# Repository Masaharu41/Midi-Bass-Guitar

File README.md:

This is the Repository for a project to create a bass guitar that features a mechanical interface that is controlled with MIDI.
  Project development was headed by Owen Fujii. The purpose of the project is to improve upon the prior MIDI controlled bass 
  guitar.

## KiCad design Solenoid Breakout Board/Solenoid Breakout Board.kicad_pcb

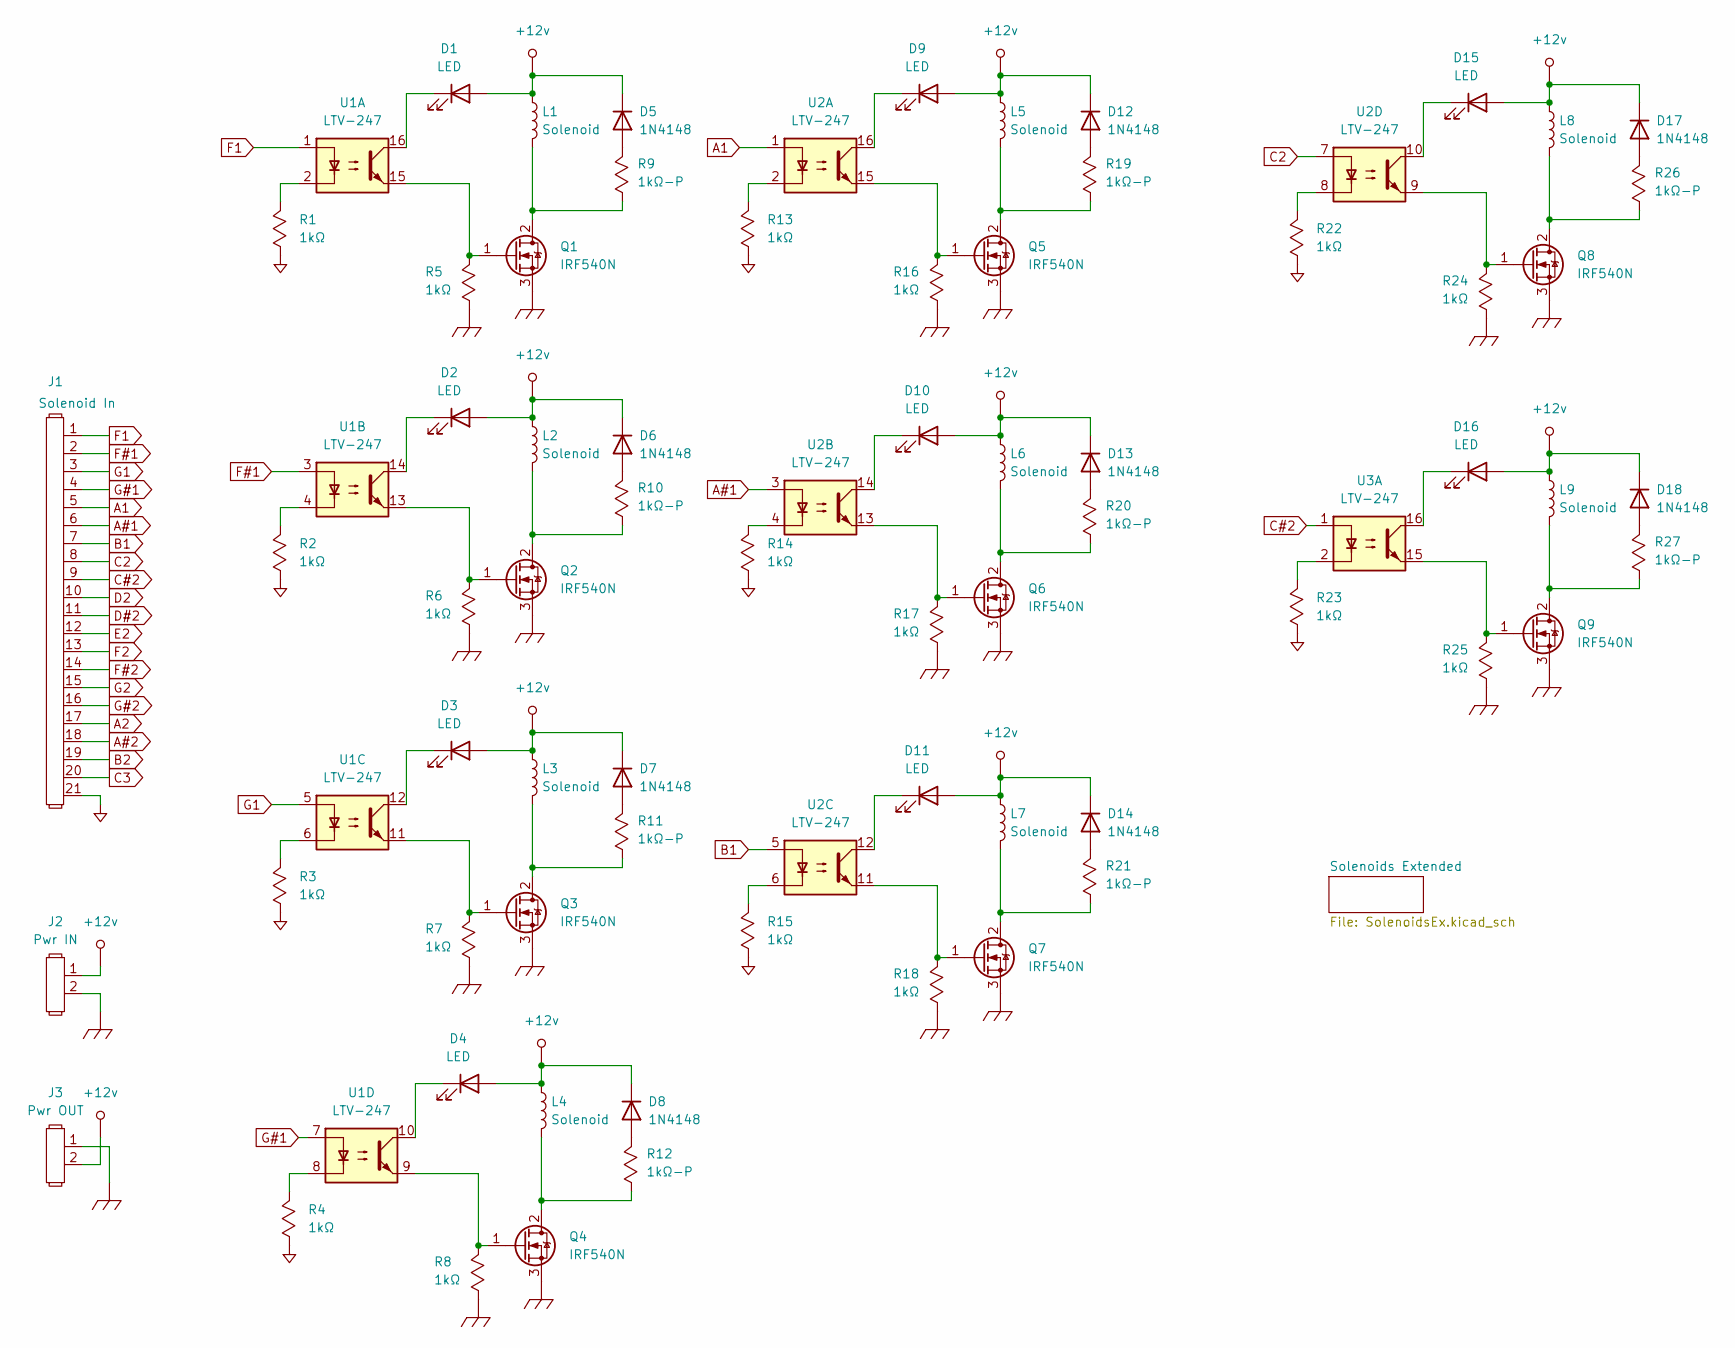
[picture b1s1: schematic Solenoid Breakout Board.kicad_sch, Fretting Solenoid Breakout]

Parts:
D1, D2, D3, D4, D9, D10, D11, D15, D16: LED; LED_0805_2012Metric_Pad1.15x1.40mm_HandSolder
D5, D6, D7, D8, D12, D13, D14, D17, D18: 1N4148; LED_0805_2012Metric_Pad1.15x1.40mm_HandSolder
J1: Solenoid In; PinHeader_1x21_P2.54mm_Vertical
J2: Pwr IN; Two_Pin_Screw_Terminal
J3: Pwr OUT; Two_Pin_Screw_Terminal
L1, L2, L3, L4, L5, L6, L7, L8, L9: Solenoid; Small Expanded TH
Q1, Q2, Q3, Q4, Q5, Q6, Q7, Q8, Q9: IRF540N; TO-220-3_Horizontal_TabUp
R1, R2, R3, R4, R5, R6, R7, R8, R13, R14, R15, R16, R17, R18, R22, R23, R24, R25: 1kΩ; R_0805_2012Metric_Pad1.20x1.40mm_HandSolder
R9, R10, R11, R12, R19, R20, R21, R26, R27: 1kΩ-P; R_1206_3216Metric_Pad1.30x1.75mm_HandSolder
U1, U2, U3: LTV-247; SOP-16_4.4x10.4mm_P1.27mm

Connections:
+12v: D1.2 (A), D2.2 (A), D3.2 (A), D4.2 (A), D5.1 (K), D6.1 (K), D7.1 (K), D8.1 (K), D9.2 (A), D10.2 (A), D11.2 (A), D12.1 (K), D13.1 (K), D14.1 (K), D15.2 (A), D16.2 (A), D17.1 (K), D18.1 (K), J2.1, J3.2, L1.1, L2.1, L3.1, L4.1, L5.1, L6.1, L7.1, L8.1, L9.1; also elsewhere on the board
A1: J1.5, U2.1
A2: J1.17; also elsewhere on the board
A#1: J1.6, U2.3
A#2: J1.18; also elsewhere on the board
B1: J1.7, U2.5
B2: J1.19; also elsewhere on the board
C2: J1.8, U2.7
C3: J1.20; also elsewhere on the board
C#2: J1.9, U3.1
Chassis_GND: J2.2, J3.1, Q1.3 (S), Q2.3 (S), Q3.3 (S), Q4.3 (S), Q5.3 (S), Q6.3 (S), Q7.3 (S), Q8.3 (S), Q9.3 (S), R5.1, R6.1, R7.1, R8.1, R16.1, R17.1, R18.1, R24.1, R25.1; also elsewhere on the board
D2: J1.10; also elsewhere on the board
D#2: J1.11; also elsewhere on the board
E2: J1.12; also elsewhere on the board
F1: J1.1, U1.1
F2: J1.13; also elsewhere on the board
F#1: J1.2, U1.3
F#2: J1.14; also elsewhere on the board
G1: J1.3, U1.5
G2: J1.15; also elsewhere on the board
G#1: J1.4, U1.7
G#2: J1.16; also elsewhere on the board
GND: J1.21, R1.1, R2.1, R3.1, R4.1, R13.1, R14.1, R15.1, R22.1, R23.1; also elsewhere on the board
unnamed: D1.1 (K), U1.16
unnamed: D2.1 (K), U1.14
unnamed: D3.1 (K), U1.12
unnamed: D4.1 (K), U1.10
unnamed: D5.2 (A), R9.2
unnamed: D6.2 (A), R10.2
unnamed: D7.2 (A), R11.2
unnamed: D8.2 (A), R12.2
unnamed: D9.1 (K), U2.16
unnamed: D10.1 (K), U2.14
unnamed: D11.1 (K), U2.12
unnamed: D12.2 (A), R19.2
unnamed: D13.2 (A), R20.2
unnamed: D14.2 (A), R21.2
unnamed: D15.1 (K), U2.10
unnamed: D16.1 (K), U3.16
unnamed: D17.2 (A), R26.2
unnamed: D18.2 (A), R27.2
unnamed: L1.2, Q1.2 (D), R9.1
unnamed: Q1.1 (G), R5.2, U1.15
unnamed: L2.2, Q2.2 (D), R10.1
unnamed: Q2.1 (G), R6.2, U1.13
unnamed: L3.2, Q3.2 (D), R11.1
unnamed: Q3.1 (G), R7.2, U1.11
unnamed: L4.2, Q4.2 (D), R12.1
unnamed: Q4.1 (G), R8.2, U1.9
unnamed: L5.2, Q5.2 (D), R19.1
unnamed: Q5.1 (G), R16.2, U2.15
unnamed: L6.2, Q6.2 (D), R20.1
unnamed: Q6.1 (G), R17.2, U2.13
unnamed: L7.2, Q7.2 (D), R21.1
unnamed: Q7.1 (G), R18.2, U2.11
unnamed: L8.2, Q8.2 (D), R26.1
unnamed: Q8.1 (G), R24.2, U2.9
unnamed: L9.2, Q9.2 (D), R27.1
unnamed: Q9.1 (G), R25.2, U3.15
unnamed: R1.2, U1.2
unnamed: R2.2, U1.4
unnamed: R3.2, U1.6
unnamed: R4.2, U1.8
unnamed: R13.2, U2.2
unnamed: R14.2, U2.4
unnamed: R15.2, U2.6
unnamed: R22.2, U2.8
unnamed: R23.2, U3.2

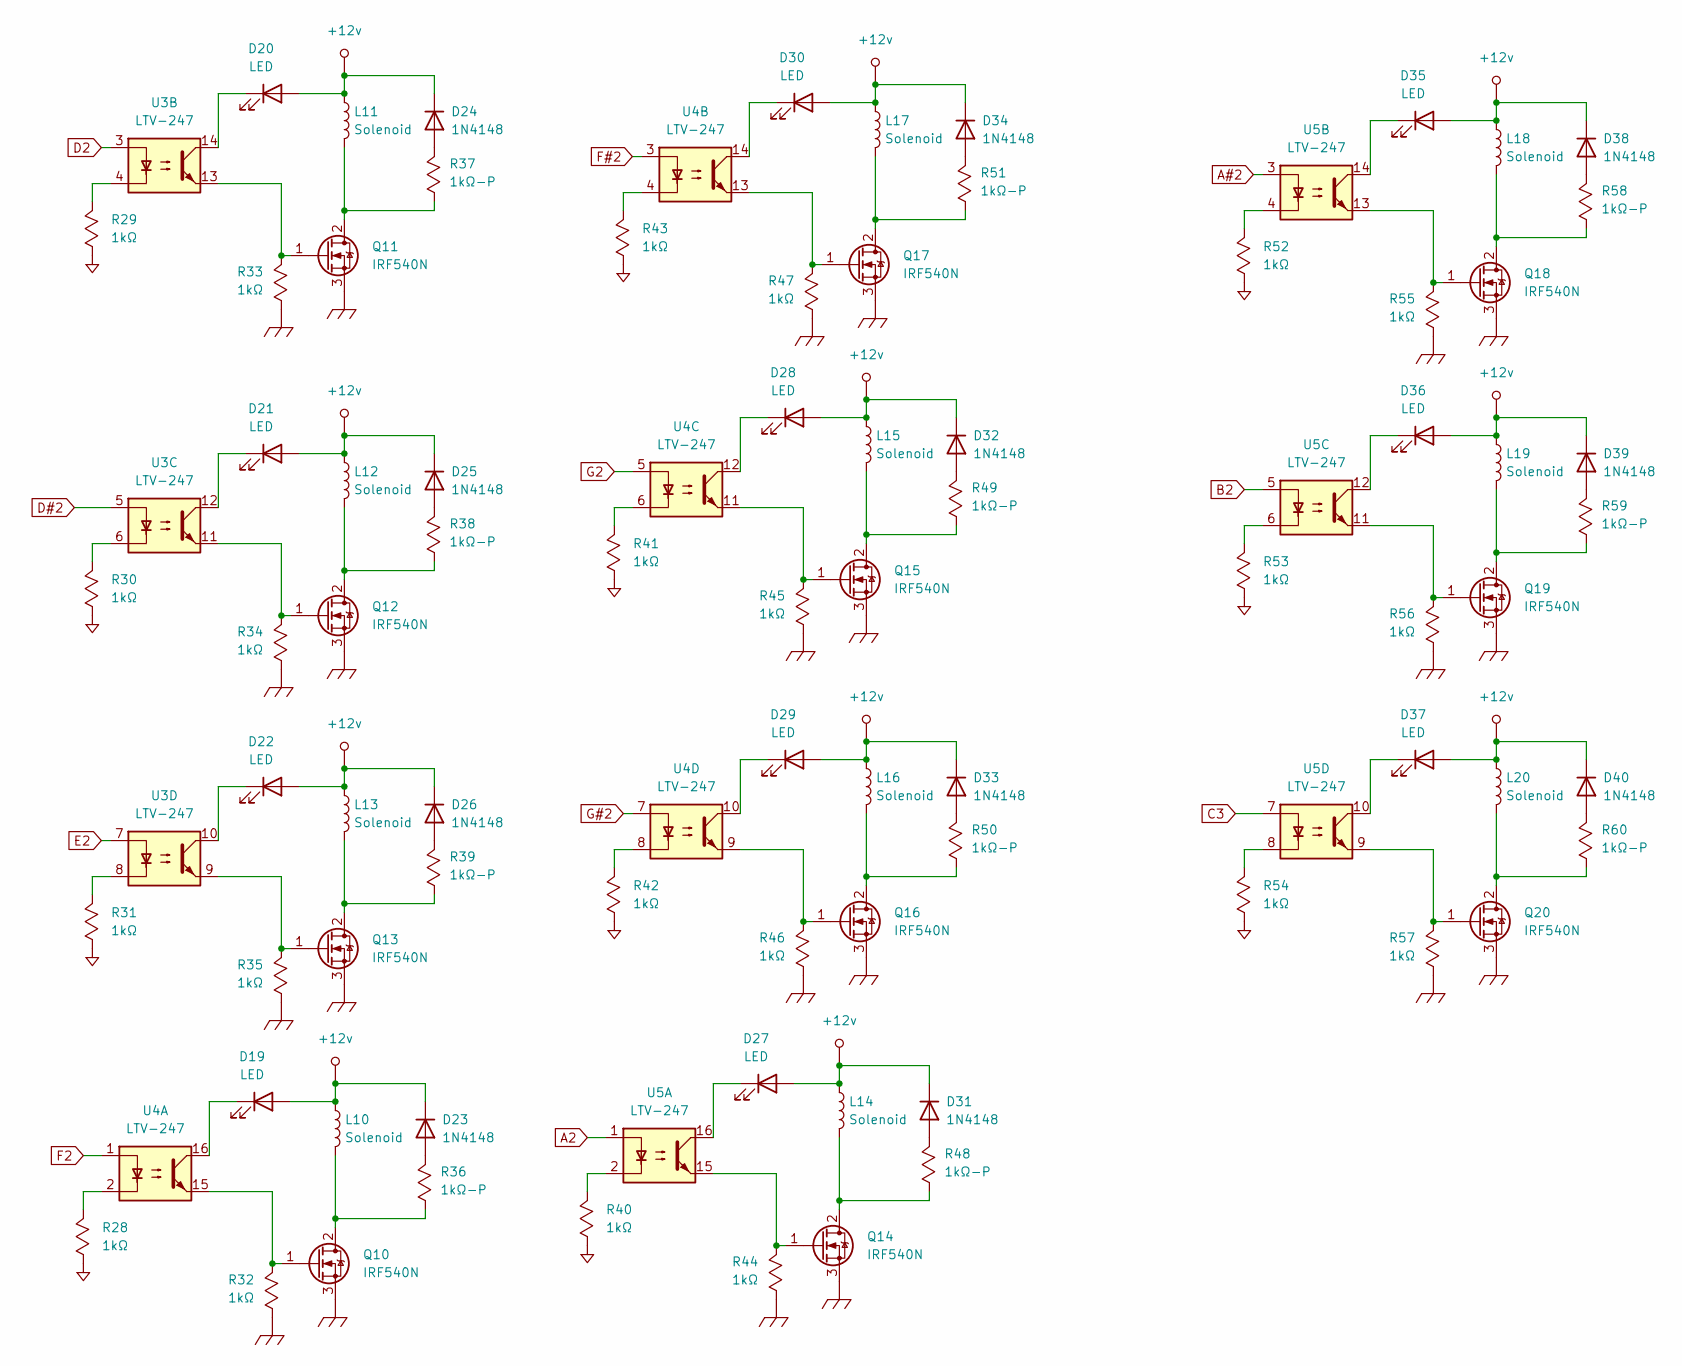
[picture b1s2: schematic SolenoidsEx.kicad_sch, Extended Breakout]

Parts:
D19, D20, D21, D22, D27, D28, D29, D30, D35, D36, D37: LED; LED_0805_2012Metric_Pad1.15x1.40mm_HandSolder
D23, D24, D25, D26, D31, D32, D33, D34, D38, D39, D40: 1N4148; LED_0805_2012Metric_Pad1.15x1.40mm_HandSolder
L10, L11, L12, L13, L14, L15, L16, L17, L18, L19, L20: Solenoid; Small Expanded TH
Q10, Q11, Q12, Q13, Q14, Q15, Q16, Q17, Q18, Q19, Q20: IRF540N; TO-220-3_Horizontal_TabUp
R28, R29, R30, R31, R32, R33, R34, R35, R40, R41, R42, R43, R44, R45, R46, R47, R52, R53, R54, R55, R56, R57: 1kΩ; R_0805_2012Metric_Pad1.20x1.40mm_HandSolder
R36, R37, R38, R39, R48, R49, R50, R51, R58, R59, R60: 1kΩ-P; R_1206_3216Metric_Pad1.30x1.75mm_HandSolder
U3, U4, U5: LTV-247; SOP-16_4.4x10.4mm_P1.27mm

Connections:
+12v: D19.2 (A), D20.2 (A), D21.2 (A), D22.2 (A), D23.1 (K), D24.1 (K), D25.1 (K), D26.1 (K), D27.2 (A), D28.2 (A), D29.2 (A), D30.2 (A), D31.1 (K), D32.1 (K), D33.1 (K), D34.1 (K), D35.2 (A), D36.2 (A), D37.2 (A), D38.1 (K), D39.1 (K), D40.1 (K), L10.1, L11.1, L12.1, L13.1, L14.1, L15.1, L16.1, L17.1, L18.1, L19.1, L20.1; also elsewhere on the board
A2: U5.1; also elsewhere on the board
A#2: U5.3; also elsewhere on the board
B2: U5.5; also elsewhere on the board
C3: U5.7; also elsewhere on the board
Chassis_GND: Q10.3 (S), Q11.3 (S), Q12.3 (S), Q13.3 (S), Q14.3 (S), Q15.3 (S), Q16.3 (S), Q17.3 (S), Q18.3 (S), Q19.3 (S), Q20.3 (S), R32.1, R33.1, R34.1, R35.1, R44.1, R45.1, R46.1, R47.1, R55.1, R56.1, R57.1; also elsewhere on the board
D2: U3.3; also elsewhere on the board
D#2: U3.5; also elsewhere on the board
E2: U3.7; also elsewhere on the board
F2: U4.1; also elsewhere on the board
F#2: U4.3; also elsewhere on the board
G2: U4.5; also elsewhere on the board
G#2: U4.7; also elsewhere on the board
GND: R28.1, R29.1, R30.1, R31.1, R40.1, R41.1, R42.1, R43.1, R52.1, R53.1, R54.1; also elsewhere on the board
unnamed: D19.1 (K), U4.16
unnamed: D20.1 (K), U3.14
unnamed: D21.1 (K), U3.12
unnamed: D22.1 (K), U3.10
unnamed: D23.2 (A), R36.2
unnamed: D24.2 (A), R37.2
unnamed: D25.2 (A), R38.2
unnamed: D26.2 (A), R39.2
unnamed: D27.1 (K), U5.16
unnamed: D28.1 (K), U4.12
unnamed: D29.1 (K), U4.10
unnamed: D30.1 (K), U4.14
unnamed: D31.2 (A), R48.2
unnamed: D32.2 (A), R49.2
unnamed: D33.2 (A), R50.2
unnamed: D34.2 (A), R51.2
unnamed: D35.1 (K), U5.14
unnamed: D36.1 (K), U5.12
unnamed: D37.1 (K), U5.10
unnamed: D38.2 (A), R58.2
unnamed: D39.2 (A), R59.2
unnamed: D40.2 (A), R60.2
unnamed: L10.2, Q10.2 (D), R36.1
unnamed: Q10.1 (G), R32.2, U4.15
unnamed: L11.2, Q11.2 (D), R37.1
unnamed: Q11.1 (G), R33.2, U3.13
unnamed: L12.2, Q12.2 (D), R38.1
unnamed: Q12.1 (G), R34.2, U3.11
unnamed: L13.2, Q13.2 (D), R39.1
unnamed: Q13.1 (G), R35.2, U3.9
unnamed: L14.2, Q14.2 (D), R48.1
unnamed: Q14.1 (G), R44.2, U5.15
unnamed: L15.2, Q15.2 (D), R49.1
unnamed: Q15.1 (G), R45.2, U4.11
unnamed: L16.2, Q16.2 (D), R50.1
unnamed: Q16.1 (G), R46.2, U4.9
unnamed: L17.2, Q17.2 (D), R51.1
unnamed: Q17.1 (G), R47.2, U4.13
unnamed: L18.2, Q18.2 (D), R58.1
unnamed: Q18.1 (G), R55.2, U5.13
unnamed: L19.2, Q19.2 (D), R59.1
unnamed: Q19.1 (G), R56.2, U5.11
unnamed: L20.2, Q20.2 (D), R60.1
unnamed: Q20.1 (G), R57.2, U5.9
unnamed: R28.2, U4.2
unnamed: R29.2, U3.4
unnamed: R30.2, U3.6
unnamed: R31.2, U3.8
unnamed: R40.2, U5.2
unnamed: R41.2, U4.6
unnamed: R42.2, U4.8
unnamed: R43.2, U4.4
unnamed: R52.2, U5.4
unnamed: R53.2, U5.6
unnamed: R54.2, U5.8

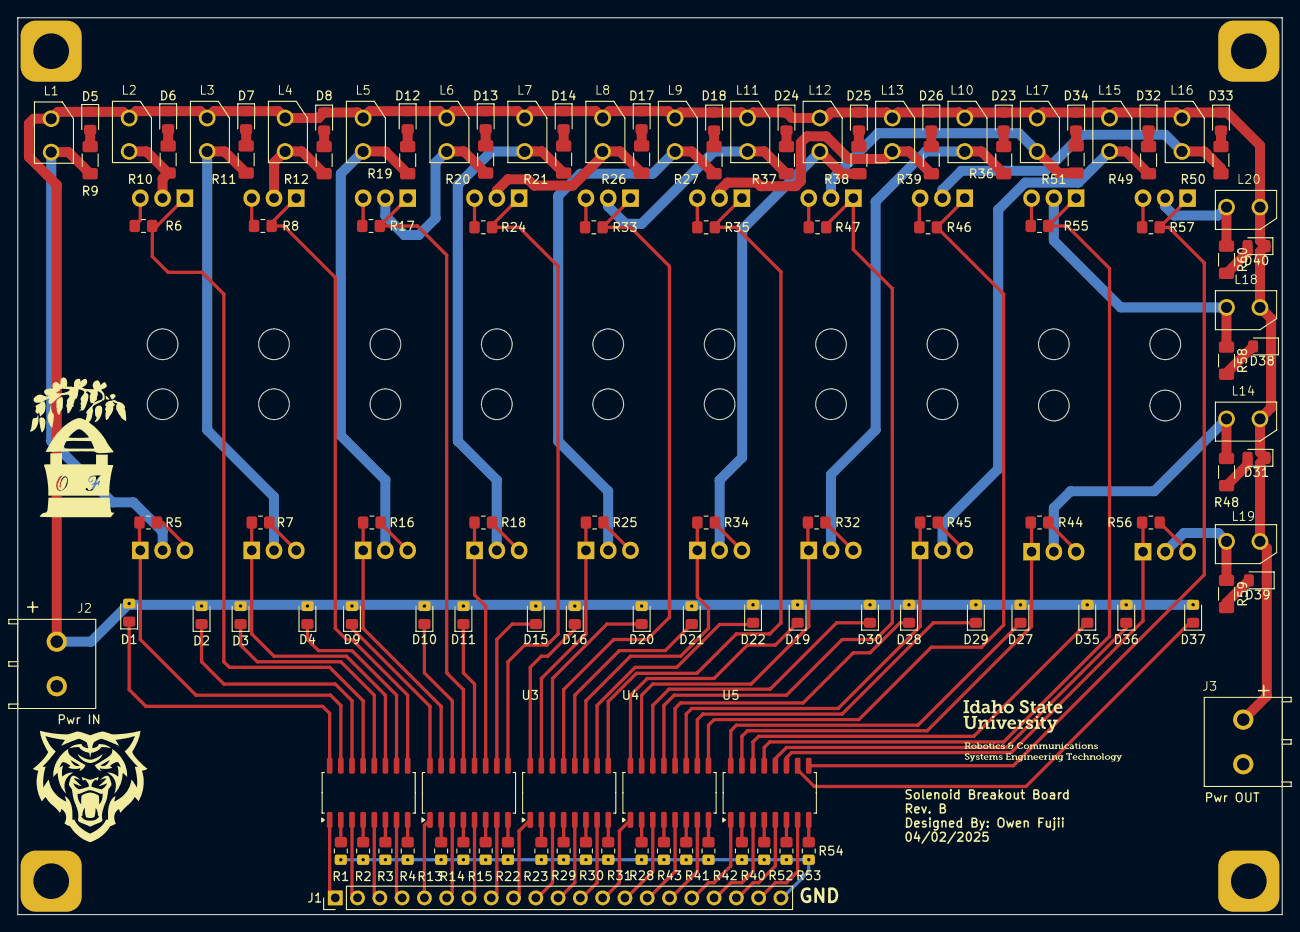
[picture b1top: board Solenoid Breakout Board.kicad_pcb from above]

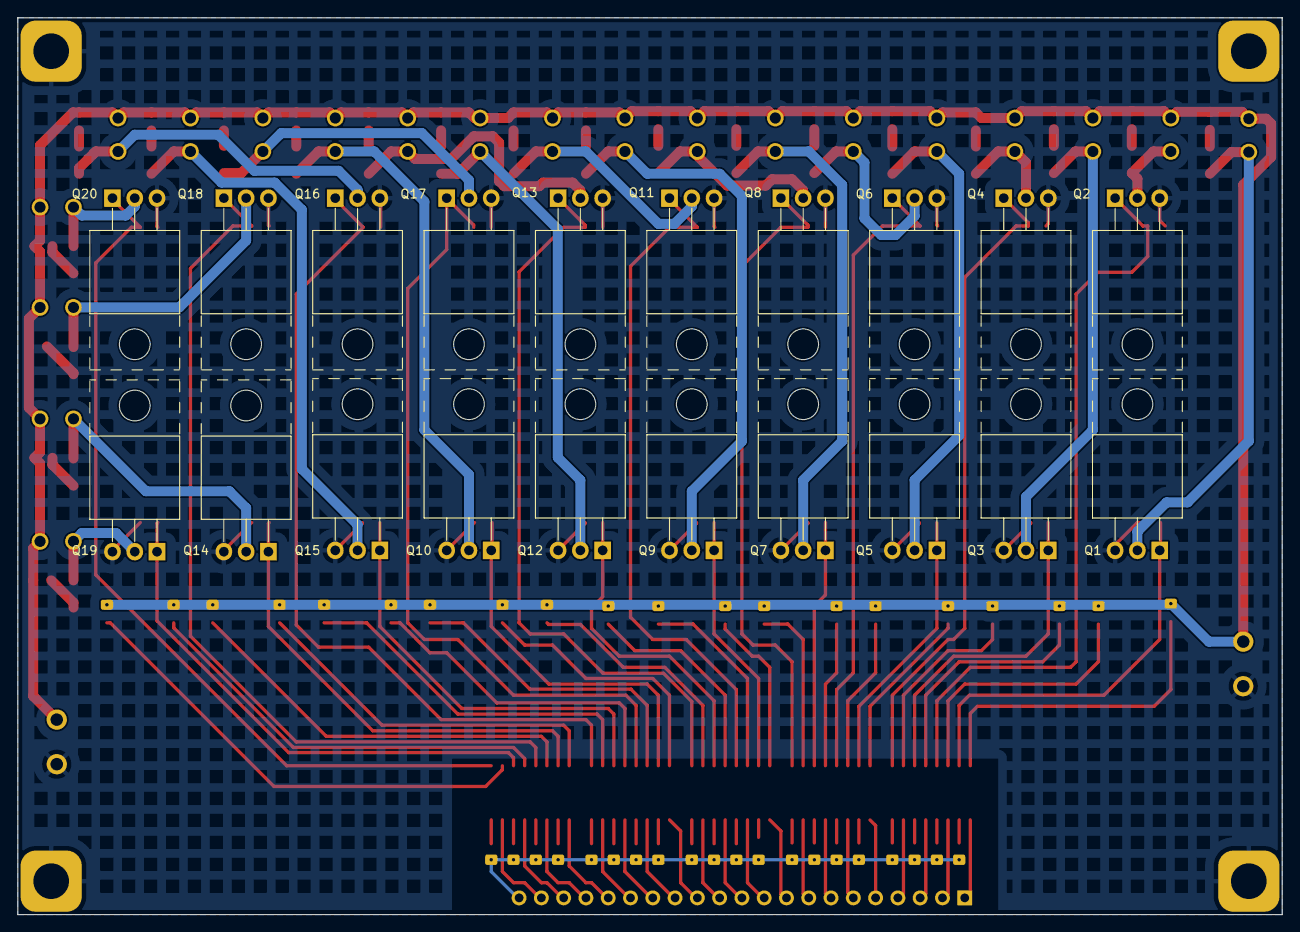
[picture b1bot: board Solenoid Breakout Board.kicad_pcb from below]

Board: 2 copper layers, 144.1 x 102.2 mm, 148 parts (20 on the bottom side), 123 nets.

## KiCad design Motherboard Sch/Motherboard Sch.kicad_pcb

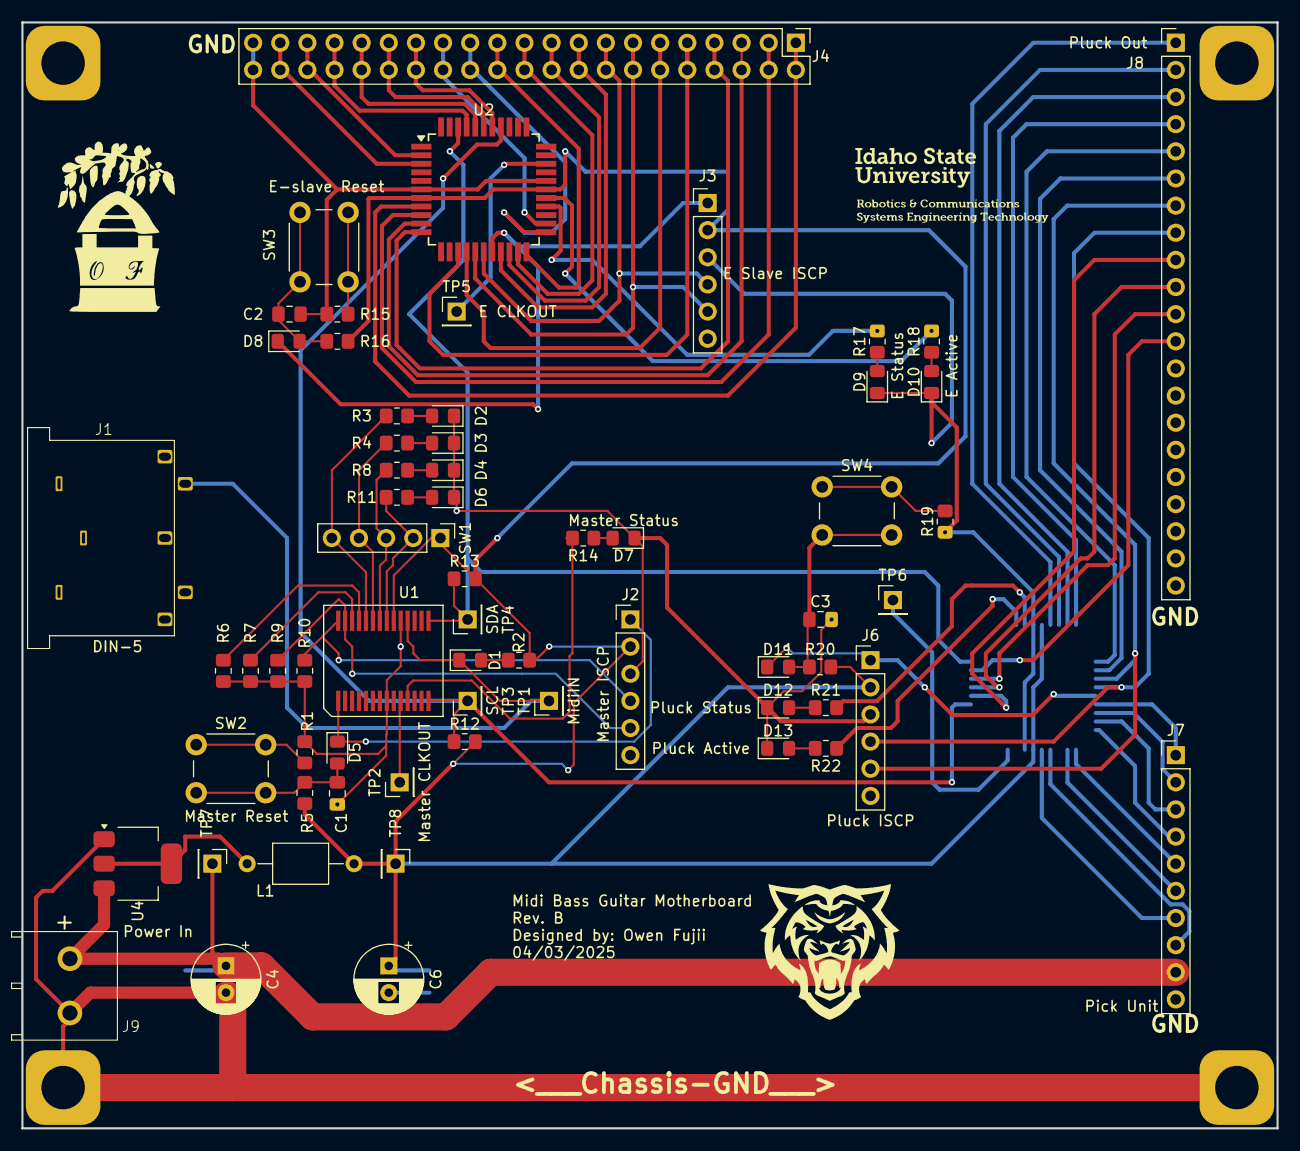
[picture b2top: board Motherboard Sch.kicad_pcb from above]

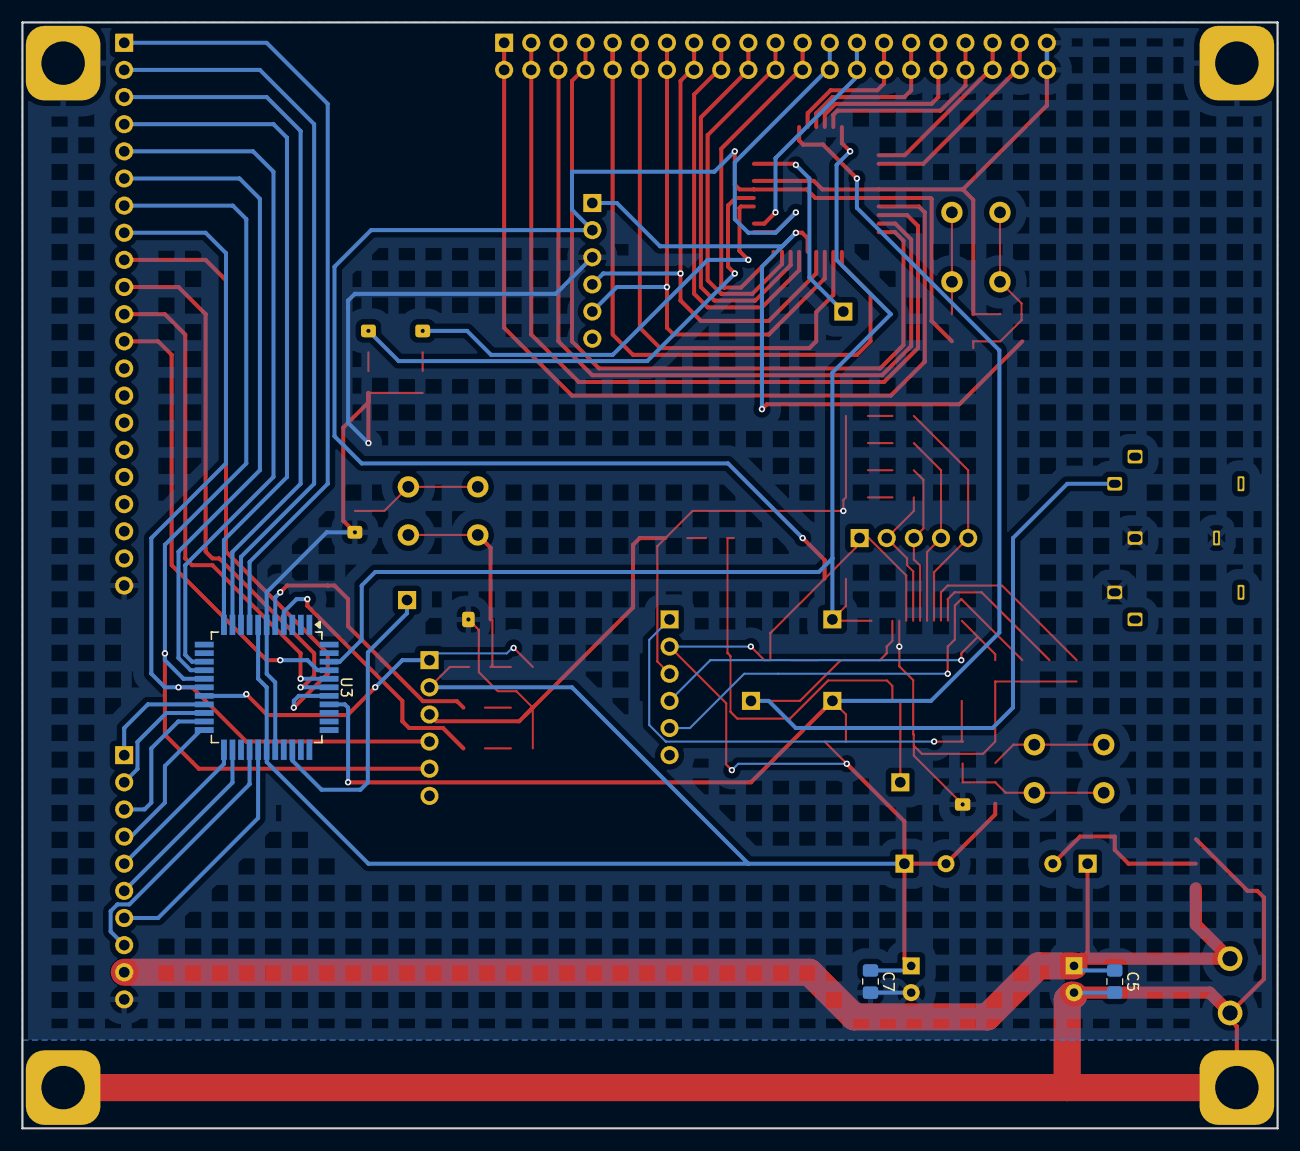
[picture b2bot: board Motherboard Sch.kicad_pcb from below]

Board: 2 copper layers, 117.5 x 103.5 mm, 67 parts (3 on the bottom side), 83 nets.

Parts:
C1, C2, C3: 10uF; C_0805_2012Metric_Pad1.18x1.45mm_HandSolder
C4, C6: 100uF; CP_Radial_D6.3mm_P2.50mm
C5, C7: 0.1uF; C_0805_2012Metric_Pad1.18x1.45mm_HandSolder
D1: LED; D_0805_2012Metric_Pad1.15x1.40mm_HandSolder
D2: 8; D_0805_2012Metric_Pad1.15x1.40mm_HandSolder
D3: 4; D_0805_2012Metric_Pad1.15x1.40mm_HandSolder
D4: 2; D_0805_2012Metric_Pad1.15x1.40mm_HandSolder
D5, D8, D11: 4148; D_0805_2012Metric_Pad1.15x1.40mm_HandSolder
D6: 1; D_0805_2012Metric_Pad1.15x1.40mm_HandSolder
D7: Master Status; D_0805_2012Metric_Pad1.15x1.40mm_HandSolder
D9: E Status; D_0805_2012Metric_Pad1.15x1.40mm_HandSolder
D10: E Active; D_0805_2012Metric_Pad1.15x1.40mm_HandSolder
D12: Pluck Status; D_0805_2012Metric_Pad1.15x1.40mm_HandSolder
D13: Pluck Active; D_0805_2012Metric_Pad1.15x1.40mm_HandSolder
J1: DIN-5; Din_5 Connector
J2: Master ISCP; PinHeader_1x06_P2.54mm_Vertical
J3: E SLAVE ISCP; PinHeader_1x06_P2.54mm_Vertical
J4: E Slave Out; PinHeader_2x21_P2.54mm_Vertical
J6: Pluck ISCP; PinHeader_1x06_P2.54mm_Vertical
J7: Pick Unit; PinHeader_1x10_P2.54mm_Vertical
J8: Pluck Out; PinHeader_1x21_P2.54mm_Vertical
J9: Power In; Two_Pin_Screw_Terminal
L1: 10uH; L_Axial_L5.0mm_D3.6mm_P10.00mm_Horizontal_Murata_BL01RN1A2A2
R1, R15, R19: 10Ω; R_0805_2012Metric_Pad1.20x1.40mm_HandSolder
R2: 1kΩ; R_0805_2012Metric_Pad1.20x1.40mm_HandSolder
R3, R4, R8, R11, R14, R17, R18, R21, R22: 330Ω; R_0805_2012Metric_Pad1.20x1.40mm_HandSolder
R5, R6, R7, R9, R10, R16, R20: 10kΩ; R_0805_2012Metric_Pad1.20x1.40mm_HandSolder
R12, R13: 2.2kΩ; R_0805_2012Metric_Pad1.20x1.40mm_HandSolder
SW1: PinHeader_1x05_P2.54mm_Vertical
SW2: Master Reset; SW_PUSH_6mm_H5mm
SW3: E-slave Reset; SW_PUSH_6mm_H5mm
SW4: Pluck Reset; SW_PUSH_6mm_H5mm
TP1: MidiIN; PinHeader_1x01_P2.54mm_Vertical
TP2: Master CLKOUT; PinHeader_1x01_P2.54mm_Vertical
TP3: SCL; PinHeader_1x01_P2.54mm_Vertical
TP4: SDA; PinHeader_1x01_P2.54mm_Vertical
TP5: E CLKOUT; PinHeader_1x01_P2.54mm_Vertical
TP6: PLUCK CLKOUT; PinHeader_1x01_P2.54mm_Vertical
TP7: P-IN; PinHeader_1x01_P2.54mm_Vertical
TP8: 5v; PinHeader_1x01_P2.54mm_Vertical
U1: PIC16F1788; SSOP-28
U2, U3: PIC16F1789; TQFP-44_10x10mm_P0.8mm_Handsolder
U4: LM1117MP-1.8; SOT-223-3_TabPin2

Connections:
1: R11.2, SW1.2 (1), U1.21 (INT/AN12/RB0)
2: R8.2, SW1.3 (2), U1.22 (P1C/AN10/RB1)
4: R4.2, SW1.4, U1.23 (P1B/AN8/RB2)
8: R3.2, SW1.5 (8), U1.24 (PGM/C12IN2-/AN8/RB3)
+5v: C6.1, C7.1, J2.2, J3.2, J6.2, L1.2, R2.2, R5.2, R12.2, R13.2, R16.2, R20.2, SW1.1 (Com), TP8.1, U1.20 (VDD), U2.7 (Vdd), U2.28 (Vdd), U3.7 (Vdd), U3.28 (Vdd)
+12v: C4.1, C5.1, J7.9, J9.1, TP7.1, U4.3 (VI)
/String Strike Slave/A0: J8.3, U3.10 (RB2/AN8/OPA2IN-/DAC3OUT1)
/String Strike Slave/A1: J8.4, U3.11 (RB3/AN9/CXNI2-/CCP2)
/String Strike Slave/A MUTE: J8.10, U3.39 (RD1/CxIN4-/OPA3OUT)
/String Strike Slave/D0: J8.5, U3.14 (RB4/AN11/C3IN1+)
/String Strike Slave/D1: J8.6, U3.15 (RB5/AN13/C4IN2-/CCP3)
/String Strike Slave/D MUTE: J8.11, U3.40 (RD2/OPA3IN-/DAC4OUT1)
/String Strike Slave/E0: J8.1, U3.8 (RB0/AN12/CCP1/C2IN1+)
/String Strike Slave/E1: J8.2, U3.9 (RB1/AN10/CxIN3-/OPA2OUT)
/String Strike Slave/E MUTE: J8.9, U3.38 (RD0/OPA3IN+)
/String Strike Slave/G MUTE: J8.12, U3.41 (RD3/PSMC4A)
A1: J4.5, U2.14 (RB4/AN11/C3IN1+)
A2: J4.17, U2.40 (RD2/OPA3IN-/DAC4OUT1)
A#1: J4.6, U2.15 (RB5/AN13/C4IN2-/CCP3)
A#2: J4.18, U2.41 (RD3/PSMC4A)
B1: J3.5, J4.7, U2.16 (RB6/C4IN1+/ICSPCLK)
B2: J4.19, U2.2 (RD4/PSM3F)
C2: J3.4, J4.8, U2.17 (RB7/DACxOUT2-/ICSPDAT)
C3: J4.20, U2.3 (RD5/PSMC3E)
C#2: J4.9, U2.19 (RA0/AN0/CxIN0-)
D2: J4.10, U2.20 (RA1/AN1/CxIN1-/OPA1OUT)
D#2: J4.11, U2.21 (RA2/AN2/CxIN0+/DAC1OUT1)
E2: J4.12, U2.22 (RA3/AN3/VREF+/C1IN1+)
Earth_GND: C4.2, C5.2, J9.2, U4.1 (GND)
F1: J4.1, U2.8 (RB0/AN12/CCP1/C2IN1+)
F2: J4.13, U2.23 (RA4/C1OUT/OPA1IN+/T0CKI)
F#1: J4.2, U2.9 (RB1/AN10/CxIN3-/OPA2OUT)
F#2: J4.14, U2.24 (RA5/AN4/C2OUT/OPA1IN+)
G1: J4.3, U2.10 (RB2/AN8/OPA2IN-/DAC3OUT1)
G2: J4.15, U2.38 (RD0/OPA3IN+)
G#1: J4.4, U2.11 (RB3/AN9/CXNI2-/CCP2)
G#2: J4.16, U2.39 (RD1/CxIN4-/OPA3OUT)
GND: C1.2, C2.2, C3.2, C6.2, C7.2, D2.1 (K), D3.1 (K), D4.1 (K), D6.1 (K), D7.1 (K), D9.1 (K), D10.1 (K), D12.1 (K), D13.1 (K), J1.2, J1.4, J1.6, J2.3, J3.3, J4.21, J6.3, J7.10, J8.21, R1.1, R6.1, R7.1, R9.1, R10.1, R15.1, R19.1, U1.8 (VSS), U1.19 (VSS), U2.6 (Vss), U2.29 (Vss), U3.6 (Vss), U3.29 (Vss)
I2Cclk: R12.1, TP3.1, U1.14 (RC3/SCK/SCL), U2.37 (RC3/SCL/SCK/PSMC1D), U3.37 (RC3/SCL/SCK/PSMC1D)
I2Cdat: R13.1, TP4.1, U1.15 (RC4/SDI/SDA), U2.42 (RC4/SDI/SDA/PSMC1E), U3.42 (RC4/SDI/SDA/PSMC1E)
MSCLR E: D8.1, J3.1, U2.18 (Vpp/~MCLR/RE3)
MSCLR P: D11.1, J6.1, U3.18 (Vpp/~MCLR/RE3)
unnamed: C1.1, D5.2, R5.1, SW2.2
unnamed: C2.1, D8.2, R16.1, SW3.2
unnamed: C3.1, D11.2, R20.1, SW4.2
unnamed: D1.2 (A), R2.1
unnamed: D1.1 (K), J1.5, TP1.1, U1.18 (RC7/RX/DT)
unnamed: D2.2 (A), R3.1
unnamed: D3.2 (A), R4.1
unnamed: D4.2 (A), R8.1
unnamed: D6.2 (A), R11.1
unnamed: D7.2 (A), R14.1
unnamed: D9.2 (A), R17.1
unnamed: D10.2 (A), R18.1
unnamed: D12.2 (A), R21.1
unnamed: D13.2 (A), R22.2
unnamed: R1.2, SW2.1
unnamed: R15.2, SW3.1
unnamed: R19.2, SW4.1
unnamed: TP2.1, U1.10 (CLKOUT/OSC2/RA6)
unnamed: R6.2, U1.25 (P1D/AN11/RB4)
unnamed: R14.2, U1.11 (RC0/T1OSO/T1CK1)
unnamed: D5.1, J2.1, U1.1 (RE3/~MCLR/Vpp)
unnamed: R7.2, U1.26 (~T1G/AN13/RB5)
unnamed: TP5.1, U2.31 (RA6/C2OUT/CLKOUT)
unnamed: R17.2, U2.26 (RE1/AN6/PSMC3B)
unnamed: R18.2, U2.27 (RE2/AN7/PSMC3A)
unnamed: J7.1, U3.19 (RA0/AN0/CxIN0-)
unnamed: J7.2, U3.20 (RA1/AN1/CxIN1-/OPA1OUT)
unnamed: J7.3, U3.21 (RA2/AN2/CxIN0+/DAC1OUT1)
unnamed: J7.4, U3.22 (RA3/AN3/VREF+/C1IN1+)
unnamed: J7.5, U3.23 (RA4/C1OUT/OPA1IN+/T0CKI)
unnamed: J7.6, U3.24 (RA5/AN4/C2OUT/OPA1IN+)
unnamed: TP6.1, U3.31 (RA6/C2OUT/CLKOUT)
unnamed: R22.1, U3.4 (RD6/PSMC3D)
unnamed: R21.2, U3.5 (RD7/C4OUT/PSMC3C)
unnamed: J7.8, U3.26 (RE1/AN6/PSMC3B)
unnamed: J7.7, U3.27 (RE2/AN7/PSMC3A)
unnamed: L1.1, U4.2 (VO)
RB6 P: J6.5, J8.7, U3.16 (RB6/C4IN1+/ICSPCLK)
RB6M: J2.5, R9.2, U1.27 (ICSPCLK/RB6)
RB7 P: J6.4, J8.8, U3.17 (RB7/DACxOUT2-/ICSPDAT)
RB7M: J2.4, R10.2, U1.28 (ICSPDAT/RB7)

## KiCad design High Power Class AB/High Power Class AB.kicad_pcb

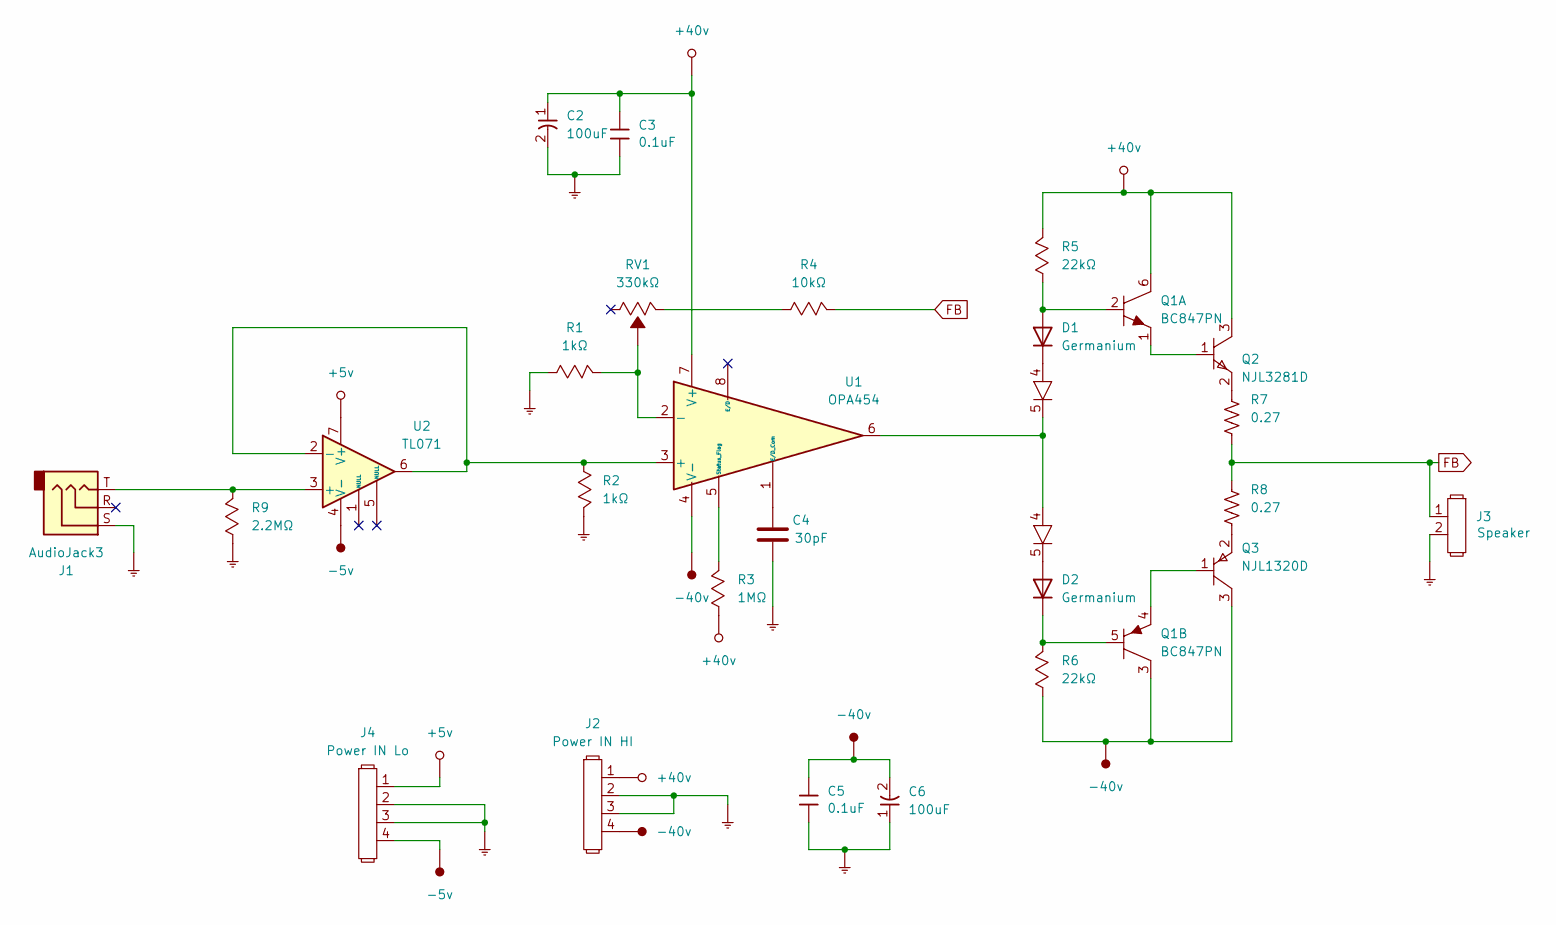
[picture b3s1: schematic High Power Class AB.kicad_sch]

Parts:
C2, C6: 100uF; CP_Radial_D10.0mm_P5.00mm
C3, C5: 0.1uF; C_0805_2012Metric_Pad1.18x1.45mm_HandSolder
C4: 30pF; C_0805_2012Metric_Pad1.18x1.45mm_HandSolder
D1, D2: Germanium; D_DO-15_P12.70mm_Horizontal
J1: AudioJack3; 1_4-input-TRS
J2: Power IN HI; 4-Pin Screw Terminal
J3: Speaker; Two_Pin_Screw_Terminal
J4: Power IN Lo; 4-Pin Screw Terminal
Q1: BC847PN; SOT-363_SC-70-6_Handsoldering
Q2: NJL3281D; TO-264-5_Vertical
Q3: NJL1320D; TO-264-5_Vertical
R1, R2: 1kΩ; R_0805_2012Metric_Pad1.20x1.40mm_HandSolder
R3: 1MΩ; R_0805_2012Metric_Pad1.20x1.40mm_HandSolder
R4: 10kΩ; R_0805_2012Metric_Pad1.20x1.40mm_HandSolder
R5, R6: 22kΩ; R_0805_2012Metric_Pad1.20x1.40mm_HandSolder
R7, R8: 0.27; R_Axial_Power_L25.0mm_W6.4mm_P27.94mm
R9: 2.2MΩ; R_0805_2012Metric_Pad1.20x1.40mm_HandSolder
RV1: 330kΩ; Potentiometer_Piher_PC-16_Single_Horizontal
U1: OPA454; SOIC-8-1EP_3.9x4.9mm_P1.27mm_EP2.29x3mm
U2: TL071; DIP-8_W7.62mm

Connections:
+5v: J4.1, U2.7 (V+)
+40v: C2.1, C3.1, J2.1, Q1.6, Q2.3, R3.1, R5.2, U1.7 (V+)
-5v: J4.4, U2.4 (V-)
-40v: C5.1, C6.2, J2.4, Q1.3, Q3.3, R6.1, U1.4 (V-)
Earth_GND: C2.2, C3.2, C4.1, C5.2, C6.1, J1.S, J2.2, J2.3, J3.2, J4.2, J4.3, R1.1, R2.2, R9.1
FB: J3.1, R4.2, R7.2, R8.1
unnamed: D1.1 (A), Q1.2, R5.1
unnamed: D1.2 (K), Q2.4
unnamed: D2.1 (A), Q3.5
unnamed: D2.2 (K), Q1.5, R6.2
unnamed: Q1.1, Q2.1
unnamed: Q1.4, Q3.1
unnamed: Q2.2, R7.1
unnamed: Q2.5, Q3.4, U1.6
unnamed: Q3.2, R8.2
unnamed: R4.1, RV1.2
unnamed: R2.1, U1.3 (+), U2.2 (-), U2.6
unnamed: R1.2, RV1.3, U1.2 (-)
unnamed: C4.2, U1.1 (E/D_Com)
unnamed: R3.2, U1.5 (Status_Flag)
unnamed: J1.T, R9.2, U2.3 (+)

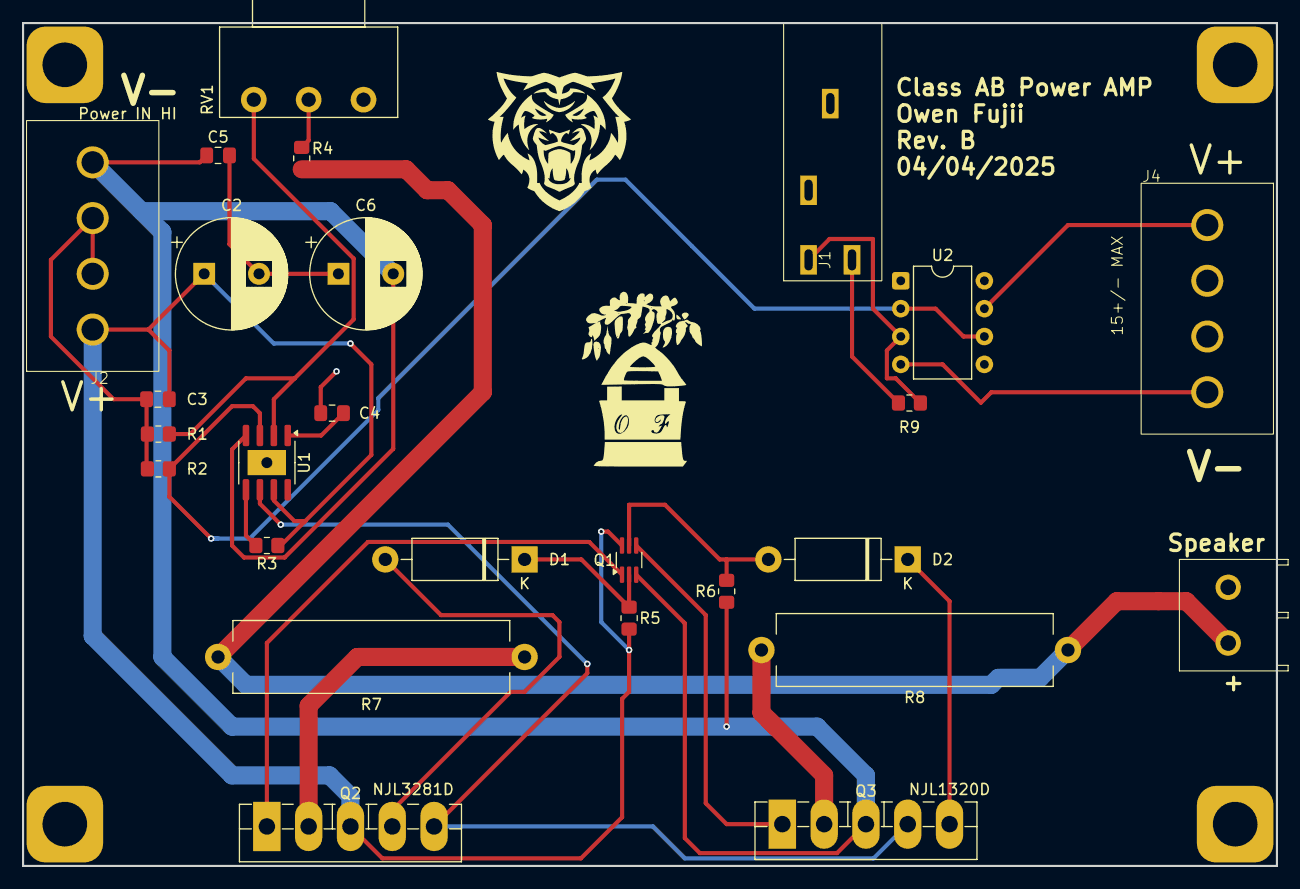
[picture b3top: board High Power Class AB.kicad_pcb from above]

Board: 2 copper layers, 114.3 x 76.8 mm, 26 parts (0 on the bottom side), 21 nets.
